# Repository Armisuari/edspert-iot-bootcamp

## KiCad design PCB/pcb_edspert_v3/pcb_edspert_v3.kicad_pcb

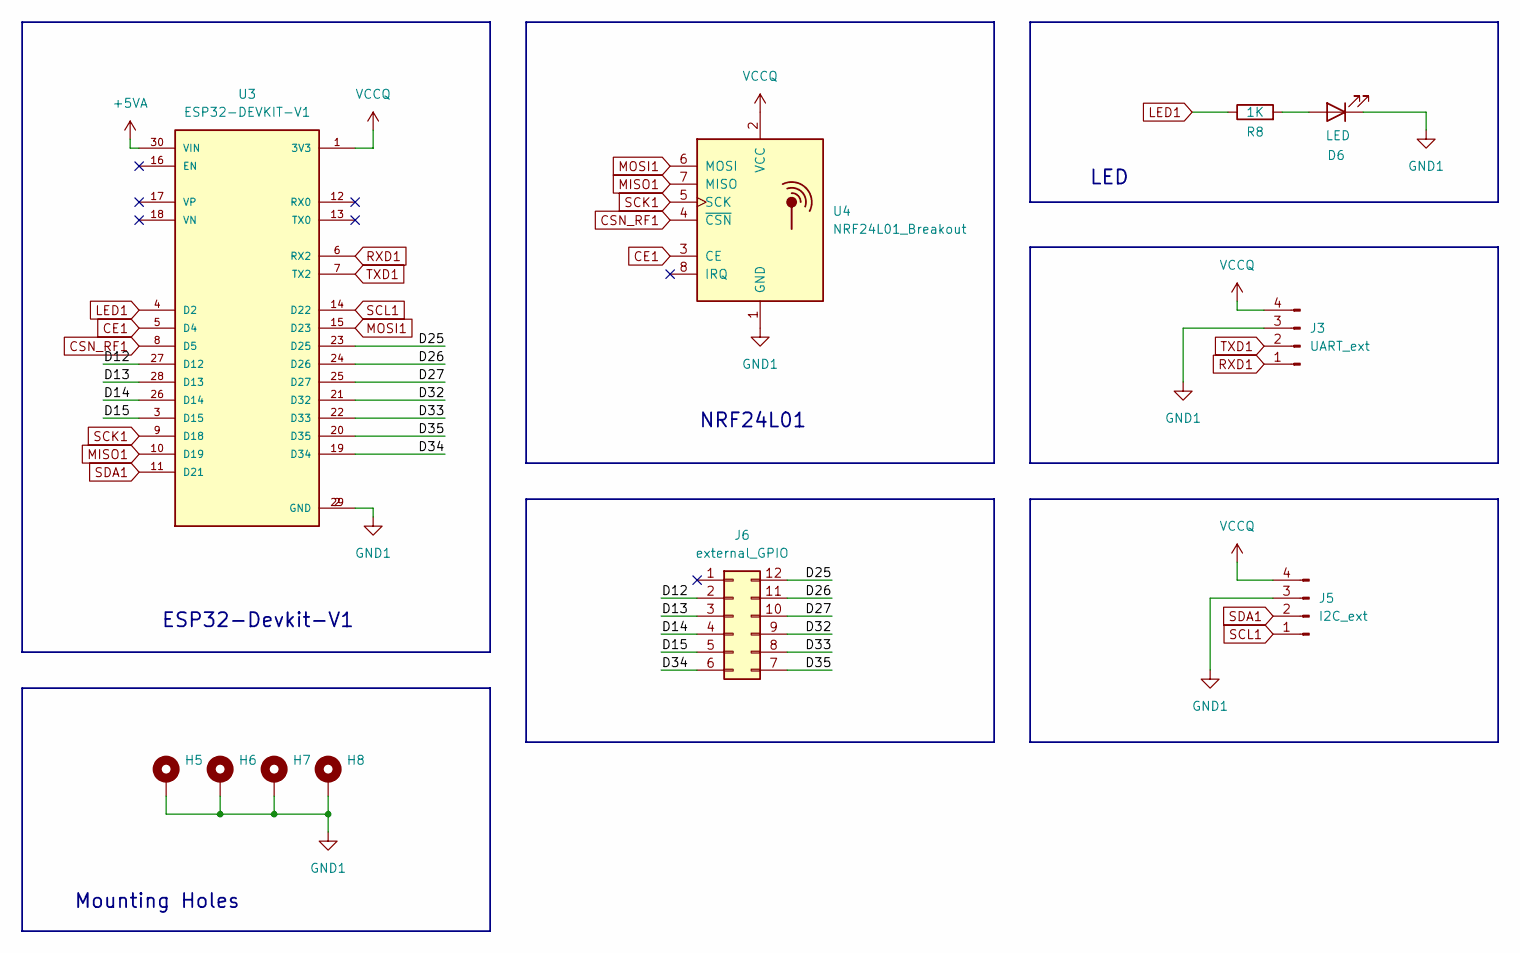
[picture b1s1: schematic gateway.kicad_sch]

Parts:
D6: LED; LED_D3.0mm_Clear
H5, H6, H7, H8: MountingHole_Pad; MountingHole_3.2mm_M3_Pad_Via
J3: UART_ext; PinHeader_1x04_P2.54mm_Vertical
J5: I2C_ext; PinHeader_1x04_P2.54mm_Vertical
J6: external_GPIO; PinHeader_2x06_P2.54mm_Vertical
R8: 1K; R_Axial_DIN0207_L6.3mm_D2.5mm_P10.16mm_Horizontal
U3: ESP32-DEVKIT-V1; MODULE_ESP32_DEVKIT_V1; PARTREV N/A
U4: NRF24L01_Breakout; nRF24L01_Breakout

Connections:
+5VA: U3.30 (VIN)
/Gateway/D12: J6.2, U3.27 (D12)
/Gateway/D13: J6.3, U3.28 (D13)
/Gateway/D14: J6.4, U3.26 (D14)
/Gateway/D15: J6.5, U3.3 (D15)
/Gateway/D25: J6.12, U3.23 (D25)
/Gateway/D26: J6.11, U3.24 (D26)
/Gateway/D27: J6.10, U3.25 (D27)
/Gateway/D32: J6.9, U3.21 (D32)
/Gateway/D33: J6.8, U3.22 (D33)
/Gateway/D34: J6.6, U3.19 (D34)
/Gateway/D35: J6.7, U3.20 (D35)
CE1: U3.5 (D4), U4.3 (CE)
CSN_RF1: U3.8 (D5), U4.4 (~CSN)
GND1: D6.1 (K), H5.1, H6.1, H7.1, H8.1, J3.3, J5.3, U3.2 (GND), U3.29 (GND), U4.1 (GND)
LED1: R8.1, U3.4 (D2)
MISO1: U3.10 (D19), U4.7 (MISO)
MOSI1: U3.15 (D23), U4.6 (MOSI)
unnamed: D6.2 (A), R8.2
RXD1: J3.1, U3.6 (RX2)
SCK1: U3.9 (D18), U4.5 (SCK)
SCL1: J5.1, U3.14 (D22)
SDA1: J5.2, U3.11 (D21)
TXD1: J3.2, U3.7 (TX2)
VCCQ: J3.4, J5.4, U3.1 (3V3), U4.2 (VCC)

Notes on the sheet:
Mounting Holes
NRF24L01
ESP32-Devkit-V1
LED

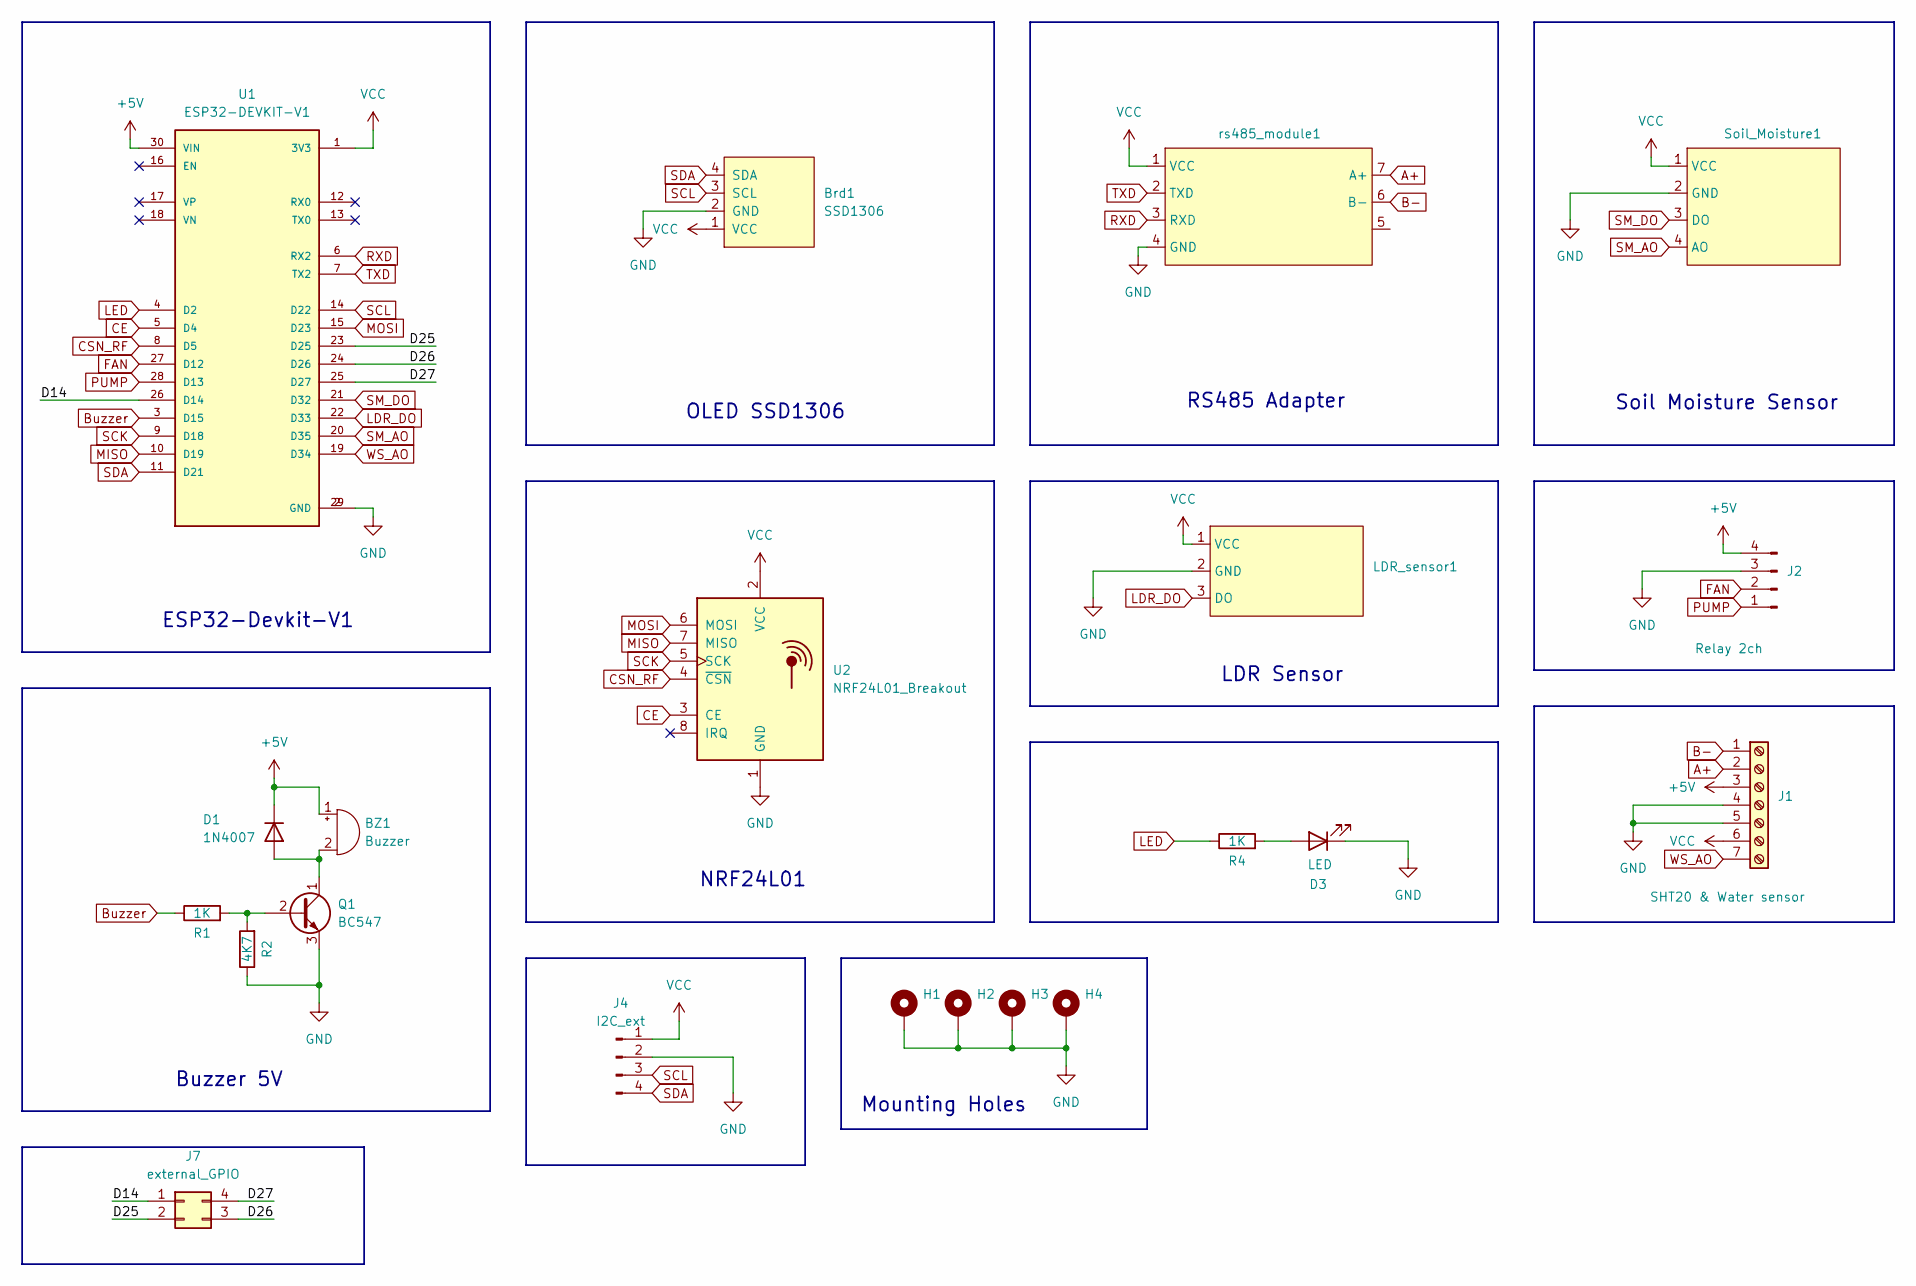
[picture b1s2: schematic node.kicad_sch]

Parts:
BZ1: Buzzer; Buzzer_12x9.5RM7.6
Brd1: SSD1306; 128x64OLED
D1: 1N4007; D_DO-41_SOD81_P10.16mm_Horizontal
D3: LED; LED_D3.0mm_Clear
H1, H2, H3, H4: MountingHole_Pad; MountingHole_3.2mm_M3_Pad_Via
J1: SHT20 & Water sensor; TerminalBlock_Phoenix_MKDS-1,5-7_1x07_P5.00mm_Horizontal
J2: Relay 2ch; PinHeader_1x04_P2.54mm_Vertical
J4: I2C_ext; PinHeader_1x04_P2.54mm_Vertical
J7: external_GPIO; PinHeader_1x04_P2.54mm_Vertical
LDR_sensor1: PinHeader_1x03_P2.54mm_Vertical
Q1: BC547; TO-92_HandSolder
R1, R4: 1K; R_Axial_DIN0207_L6.3mm_D2.5mm_P10.16mm_Horizontal
R2: 4K7; R_Axial_DIN0207_L6.3mm_D2.5mm_P10.16mm_Horizontal
Soil_Moisture1: PinHeader_1x04_P2.54mm_Vertical
U1: ESP32-DEVKIT-V1; MODULE_ESP32_DEVKIT_V1; PARTREV N/A
U2: NRF24L01_Breakout; nRF24L01_Breakout
rs485_module1: rs485_module

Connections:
+5V: BZ1.1 (+), D1.1 (K), J1.3, J2.4, U1.30 (VIN)
/Node/D14: J7.1, U1.26 (D14)
/Node/D25: J7.2, U1.23 (D25)
/Node/D26: J7.3, U1.24 (D26)
/Node/D27: J7.4, U1.25 (D27)
A+: J1.2, rs485_module1.7 (A+)
B-: J1.1, rs485_module1.6 (B-)
Buzzer: R1.1, U1.3 (D15)
CE: U1.5 (D4), U2.3 (CE)
CSN_RF: U1.8 (D5), U2.4 (~CSN)
FAN: J2.2, U1.27 (D12)
GND: Brd1.2 (GND), D3.1 (K), H1.1, H2.1, H3.1, H4.1, J1.4, J1.5, J2.3, J4.2, LDR_sensor1.2 (GND), Q1.3 (E), R2.1, Soil_Moisture1.2 (GND), U1.2 (GND), U1.29 (GND), U2.1 (GND), rs485_module1.4 (GND); also elsewhere on the board
LDR_DO: LDR_sensor1.3 (DO), U1.22 (D33); also elsewhere on the board
LED: R4.1, U1.4 (D2)
MISO: U1.10 (D19), U2.7 (MISO)
MOSI: U1.15 (D23), U2.6 (MOSI)
unnamed: BZ1.2 (-), D1.2 (A), Q1.1 (C)
unnamed: D3.2 (A), R4.2
unnamed: Q1.2 (B), R1.2, R2.2
PUMP: J2.1, U1.28 (D13)
RXD: U1.6 (RX2), rs485_module1.3 (RXD)
SCK: U1.9 (D18), U2.5 (SCK)
SCL: Brd1.3 (SCL), J4.3, U1.14 (D22)
SDA: Brd1.4 (SDA), J4.4, U1.11 (D21)
SM_AO: Soil_Moisture1.4 (AO), U1.20 (D35); also elsewhere on the board
SM_DO: Soil_Moisture1.3 (DO), U1.21 (D32); also elsewhere on the board
TXD: U1.7 (TX2), rs485_module1.2 (TXD)
VCC: Brd1.1 (VCC), J1.6, J4.1, LDR_sensor1.1 (VCC), Soil_Moisture1.1 (VCC), U1.1 (3V3), U2.2 (VCC), rs485_module1.1 (VCC); also elsewhere on the board
WS_AO: J1.7, U1.19 (D34)

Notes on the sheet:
Mounting Holes
Soil Moisture Sensor
Buzzer 5V
OLED SSD1306
RS485 Adapter
NRF24L01
ESP32-Devkit-V1
LDR Sensor

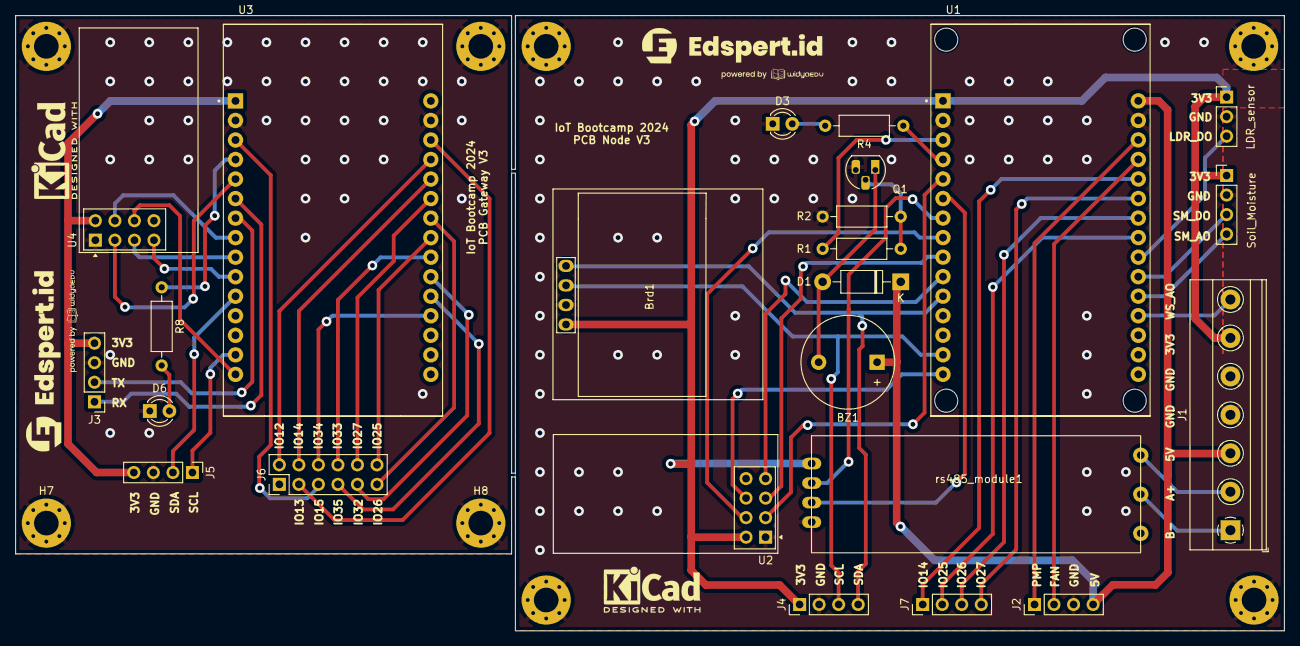
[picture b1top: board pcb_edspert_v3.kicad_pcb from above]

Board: 2 copper layers, 165.0 x 80.0 mm, 32 parts (0 on the bottom side), 53 nets.

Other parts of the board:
LDR_sensor: PinHeader_1x03_P2.54mm_Vertical
Soil_Moisture: PinHeader_1x04_P2.54mm_Vertical

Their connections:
GND: LDR_sensor.2 (GND), Soil_Moisture.2 (GND); also elsewhere on the board
LDR_DO: LDR_sensor.3 (DO); also elsewhere on the board
SM_AO: Soil_Moisture.4 (AO); also elsewhere on the board
SM_DO: Soil_Moisture.3 (DO); also elsewhere on the board
VCC: LDR_sensor.1 (VCC), Soil_Moisture.1 (VCC); also elsewhere on the board

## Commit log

2024-08-24 feat : add bmp180 library
2024-08-24 feat : add PCB design
2024-08-24 feat : add water level sensor library
2024-08-26 Create Showcase_Sensor&Aktuator
2024-08-26 Rename Showcase_Sensor&Aktuator to Showcase_Sensor&Aktuat.mdor
2024-08-26 Rename Showcase_Sensor&Aktuat.mdor to Showcase_Sensor&Aktuator.md
2024-08-29 Rename Read_LDR_Sensor.ino to Read_LDR_Sensor.ino
2024-08-29 update module 3 codes
2024-08-30 update the codes
2024-09-09 add custom library soil moisture sensor
2024-09-09 add custom library sht20 modbus sensor
2024-09-09 add source code final project
2024-11-03 add 8.1 codes
2024-11-03 add 8.2 codes
2024-11-13 add module 11 mit app inventor code
2025-01-09 remove unnecessary codes
